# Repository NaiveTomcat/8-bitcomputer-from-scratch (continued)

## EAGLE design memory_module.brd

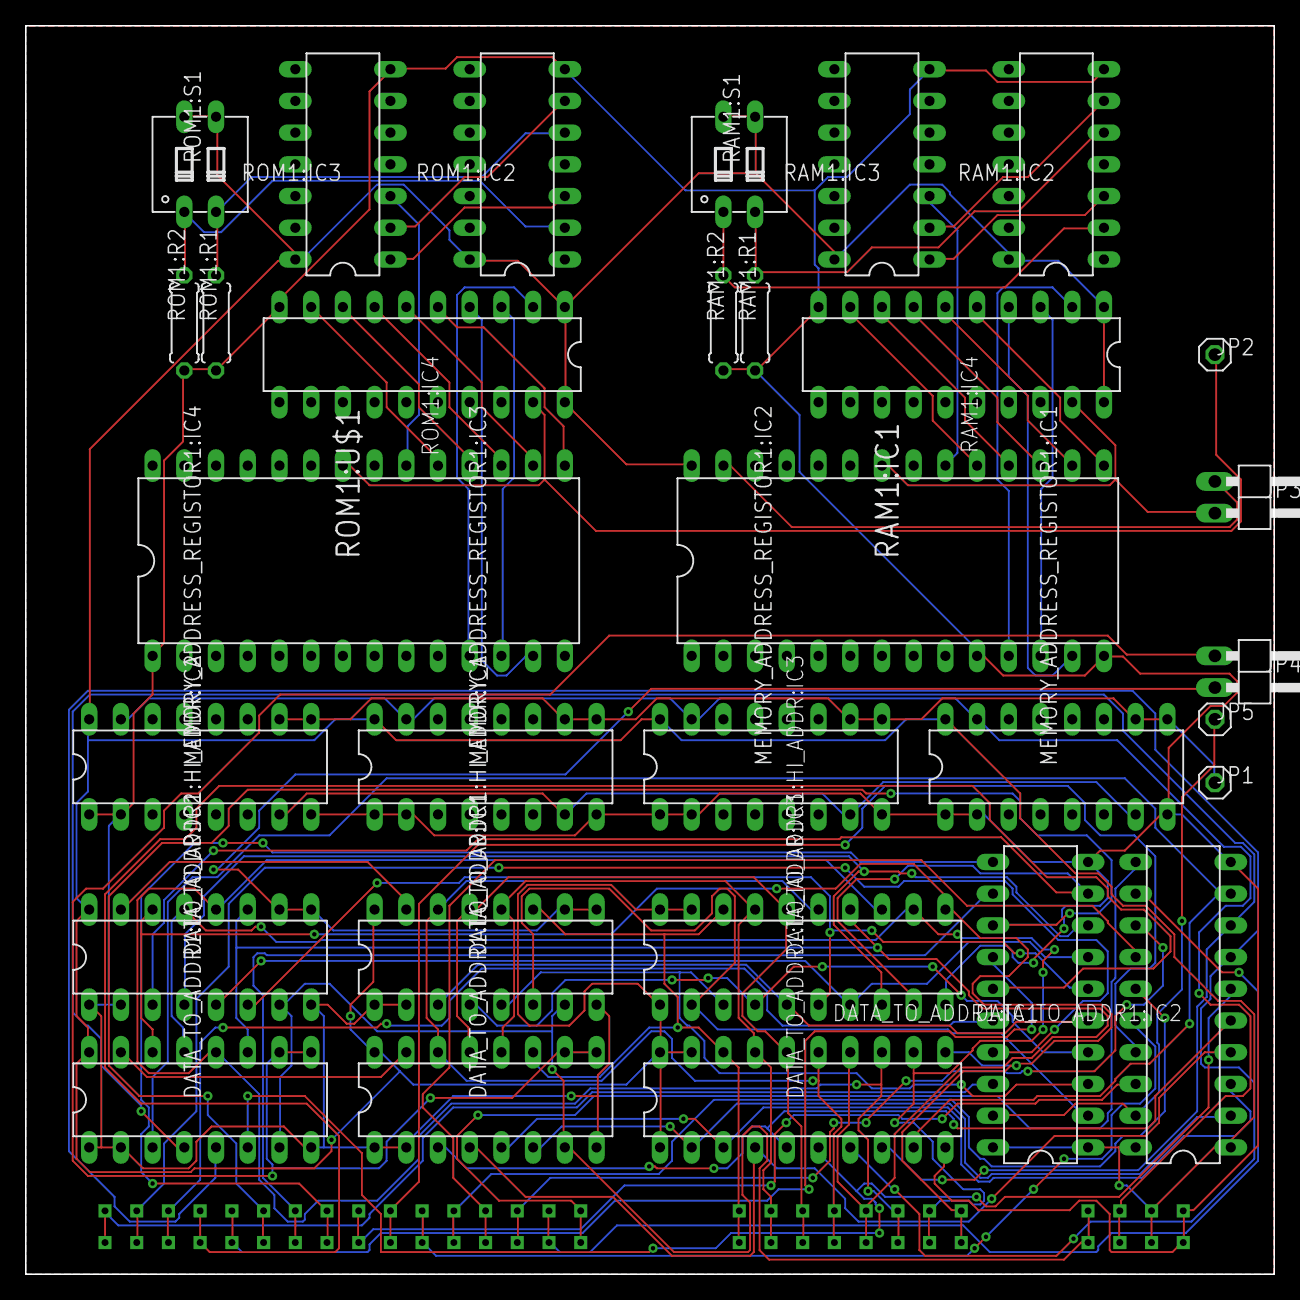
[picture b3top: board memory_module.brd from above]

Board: 2 copper layers, 100.0 x 100.0 mm, 32 parts (0 on the bottom side), 80 nets.

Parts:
DATA_TO_ADDR1:HI_ADDR:IC1, DATA_TO_ADDR1:HI_ADDR:IC2, DATA_TO_ADDR1:LO_ADDR:IC1, DATA_TO_ADDR1:LO_ADDR:IC2: 74LS173N; DIL16
DATA_TO_ADDR1:HI_ADDR:IC3, DATA_TO_ADDR1:IC1, DATA_TO_ADDR1:IC2, DATA_TO_ADDR1:LO_ADDR:IC3: 74LS245N; DIL20
JP1, JP2, JP5: 1X01
JP3, JP4: 1X02/90
MEMORY_ADDRESS_REGISTOR1:IC1, MEMORY_ADDRESS_REGISTOR1:IC2, MEMORY_ADDRESS_REGISTOR1:IC3, MEMORY_ADDRESS_REGISTOR1:IC4: 74LS173N; DIL16
RAM1:IC1: CY62256LL-PC; DIL28-6
RAM1:IC2: 74LS86N; DIL14
RAM1:IC3: 7432N; DIL14
RAM1:IC4: 74LS245N; DIL20
RAM1:R1, RAM1:R2: 0207/7
RAM1:S1: DIP02YL
ROM1:IC2: 74LS86N; DIL14
ROM1:IC3: 7432N; DIL14
ROM1:IC4: 74LS245N; DIL20
ROM1:R1, ROM1:R2: 0207/7
ROM1:S1: DIP02YL
ROM1:U$1: AT28C256-28DIP; DIL28-6
U$1: PORT_BOARD; PORT_FOOTPT

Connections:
!D2AHI: DATA_TO_ADDR1:HI_ADDR:IC1.9, DATA_TO_ADDR1:HI_ADDR:IC1.10, DATA_TO_ADDR1:HI_ADDR:IC2.9, DATA_TO_ADDR1:HI_ADDR:IC2.10, JP4.2
!D2ALI: DATA_TO_ADDR1:LO_ADDR:IC1.9, DATA_TO_ADDR1:LO_ADDR:IC1.10, DATA_TO_ADDR1:LO_ADDR:IC2.9, DATA_TO_ADDR1:LO_ADDR:IC2.10, JP4.1
!D2AO: DATA_TO_ADDR1:IC1.19, DATA_TO_ADDR1:IC2.19, JP5.1
!MARI: JP1.1, MEMORY_ADDRESS_REGISTOR1:IC1.9, MEMORY_ADDRESS_REGISTOR1:IC1.10, MEMORY_ADDRESS_REGISTOR1:IC2.9, MEMORY_ADDRESS_REGISTOR1:IC2.10, MEMORY_ADDRESS_REGISTOR1:IC3.9, MEMORY_ADDRESS_REGISTOR1:IC3.10, MEMORY_ADDRESS_REGISTOR1:IC4.9, MEMORY_ADDRESS_REGISTOR1:IC4.10
!RAMO: JP3.2, RAM1:IC1.22, RAM1:IC4.19
!RAMW: JP3.1, RAM1:IC1.27
!ROMO: JP2.1, ROM1:IC4.19, ROM1:U$1.22
A0: DATA_TO_ADDR1:IC1.18, U$1.A0, U$1.A16
A1: DATA_TO_ADDR1:IC1.17, U$1.A1, U$1.A17
A2: DATA_TO_ADDR1:IC1.16, U$1.A2, U$1.A18
A3: DATA_TO_ADDR1:IC1.15, U$1.A3, U$1.A19
A4: DATA_TO_ADDR1:IC1.14, U$1.A4, U$1.A20
A5: DATA_TO_ADDR1:IC1.13, U$1.A5, U$1.A21
A6: DATA_TO_ADDR1:IC1.12, U$1.A6, U$1.A22
A7: DATA_TO_ADDR1:IC1.11, U$1.A7, U$1.A23
A8: DATA_TO_ADDR1:IC2.18, U$1.A8, U$1.A24
A9: DATA_TO_ADDR1:IC2.17, U$1.A9, U$1.A25
A10: DATA_TO_ADDR1:IC2.16, U$1.A10, U$1.A26
A11: DATA_TO_ADDR1:IC2.15, U$1.A11, U$1.A27
A12: DATA_TO_ADDR1:IC2.14, U$1.A12, U$1.A28
A13: DATA_TO_ADDR1:IC2.13, U$1.A13, U$1.A29
A14: DATA_TO_ADDR1:IC2.12, U$1.A14, U$1.A30
A15: DATA_TO_ADDR1:IC2.11, U$1.A15, U$1.A31
CLOCK: DATA_TO_ADDR1:HI_ADDR:IC1.7, DATA_TO_ADDR1:HI_ADDR:IC2.7, DATA_TO_ADDR1:LO_ADDR:IC1.7, DATA_TO_ADDR1:LO_ADDR:IC2.7, U$1.CLK, U$1.CLK1
DATA_0: DATA_TO_ADDR1:HI_ADDR:IC1.11, DATA_TO_ADDR1:HI_ADDR:IC3.18, DATA_TO_ADDR1:LO_ADDR:IC1.11, DATA_TO_ADDR1:LO_ADDR:IC3.18, U$1.D0, U$1.D8
DATA_1: DATA_TO_ADDR1:HI_ADDR:IC1.12, DATA_TO_ADDR1:HI_ADDR:IC3.17, DATA_TO_ADDR1:LO_ADDR:IC1.12, DATA_TO_ADDR1:LO_ADDR:IC3.17, U$1.D1, U$1.D9
DATA_2: DATA_TO_ADDR1:HI_ADDR:IC1.13, DATA_TO_ADDR1:HI_ADDR:IC3.16, DATA_TO_ADDR1:LO_ADDR:IC1.13, DATA_TO_ADDR1:LO_ADDR:IC3.16, U$1.D2, U$1.D10
DATA_3: DATA_TO_ADDR1:HI_ADDR:IC1.14, DATA_TO_ADDR1:HI_ADDR:IC3.15, DATA_TO_ADDR1:LO_ADDR:IC1.14, DATA_TO_ADDR1:LO_ADDR:IC3.15, U$1.D3, U$1.D11
DATA_4: DATA_TO_ADDR1:HI_ADDR:IC2.11, DATA_TO_ADDR1:HI_ADDR:IC3.14, DATA_TO_ADDR1:LO_ADDR:IC2.11, DATA_TO_ADDR1:LO_ADDR:IC3.14, U$1.D4, U$1.D12
DATA_5: DATA_TO_ADDR1:HI_ADDR:IC2.12, DATA_TO_ADDR1:HI_ADDR:IC3.13, DATA_TO_ADDR1:LO_ADDR:IC2.12, DATA_TO_ADDR1:LO_ADDR:IC3.13, U$1.D5, U$1.D13
DATA_6: DATA_TO_ADDR1:HI_ADDR:IC2.13, DATA_TO_ADDR1:HI_ADDR:IC3.12, DATA_TO_ADDR1:LO_ADDR:IC2.13, DATA_TO_ADDR1:LO_ADDR:IC3.12, U$1.D6, U$1.D14
DATA_7: DATA_TO_ADDR1:HI_ADDR:IC2.14, DATA_TO_ADDR1:HI_ADDR:IC3.11, DATA_TO_ADDR1:LO_ADDR:IC2.14, DATA_TO_ADDR1:LO_ADDR:IC3.11, U$1.D7, U$1.D15
DATA_TO_ADDR1:HI_ADDR:CLR: DATA_TO_ADDR1:HI_ADDR:IC1.15, DATA_TO_ADDR1:HI_ADDR:IC2.15
DATA_TO_ADDR1:LO_ADDR:CLR: DATA_TO_ADDR1:LO_ADDR:IC1.15, DATA_TO_ADDR1:LO_ADDR:IC2.15
DATA_TO_ADDR1:N$16: DATA_TO_ADDR1:HI_ADDR:IC1.6, DATA_TO_ADDR1:HI_ADDR:IC3.2, DATA_TO_ADDR1:IC1.2
DATA_TO_ADDR1:N$17: DATA_TO_ADDR1:HI_ADDR:IC1.5, DATA_TO_ADDR1:HI_ADDR:IC3.3, DATA_TO_ADDR1:IC1.3
DATA_TO_ADDR1:N$18: DATA_TO_ADDR1:HI_ADDR:IC1.4, DATA_TO_ADDR1:HI_ADDR:IC3.4, DATA_TO_ADDR1:IC1.4
DATA_TO_ADDR1:N$19: DATA_TO_ADDR1:HI_ADDR:IC1.3, DATA_TO_ADDR1:HI_ADDR:IC3.5, DATA_TO_ADDR1:IC1.5
DATA_TO_ADDR1:N$20: DATA_TO_ADDR1:HI_ADDR:IC2.6, DATA_TO_ADDR1:HI_ADDR:IC3.6, DATA_TO_ADDR1:IC1.6
DATA_TO_ADDR1:N$21: DATA_TO_ADDR1:HI_ADDR:IC2.5, DATA_TO_ADDR1:HI_ADDR:IC3.7, DATA_TO_ADDR1:IC1.7
DATA_TO_ADDR1:N$22: DATA_TO_ADDR1:HI_ADDR:IC2.4, DATA_TO_ADDR1:HI_ADDR:IC3.8, DATA_TO_ADDR1:IC1.8
DATA_TO_ADDR1:N$23: DATA_TO_ADDR1:HI_ADDR:IC2.3, DATA_TO_ADDR1:HI_ADDR:IC3.9, DATA_TO_ADDR1:IC1.9
DATA_TO_ADDR1:N$24: DATA_TO_ADDR1:IC2.2, DATA_TO_ADDR1:LO_ADDR:IC1.6, DATA_TO_ADDR1:LO_ADDR:IC3.2
DATA_TO_ADDR1:N$25: DATA_TO_ADDR1:IC2.3, DATA_TO_ADDR1:LO_ADDR:IC1.5, DATA_TO_ADDR1:LO_ADDR:IC3.3
DATA_TO_ADDR1:N$26: DATA_TO_ADDR1:IC2.4, DATA_TO_ADDR1:LO_ADDR:IC1.4, DATA_TO_ADDR1:LO_ADDR:IC3.4
DATA_TO_ADDR1:N$27: DATA_TO_ADDR1:IC2.5, DATA_TO_ADDR1:LO_ADDR:IC1.3, DATA_TO_ADDR1:LO_ADDR:IC3.5
DATA_TO_ADDR1:N$28: DATA_TO_ADDR1:IC2.6, DATA_TO_ADDR1:LO_ADDR:IC2.6, DATA_TO_ADDR1:LO_ADDR:IC3.6
DATA_TO_ADDR1:N$29: DATA_TO_ADDR1:IC2.7, DATA_TO_ADDR1:LO_ADDR:IC2.5, DATA_TO_ADDR1:LO_ADDR:IC3.7
DATA_TO_ADDR1:N$30: DATA_TO_ADDR1:IC2.8, DATA_TO_ADDR1:LO_ADDR:IC2.4, DATA_TO_ADDR1:LO_ADDR:IC3.8
DATA_TO_ADDR1:N$31: DATA_TO_ADDR1:IC2.9, DATA_TO_ADDR1:LO_ADDR:IC2.3, DATA_TO_ADDR1:LO_ADDR:IC3.9
GND: DATA_TO_ADDR1:HI_ADDR:IC1.1, DATA_TO_ADDR1:HI_ADDR:IC1.2, DATA_TO_ADDR1:HI_ADDR:IC1.8, DATA_TO_ADDR1:HI_ADDR:IC2.1, DATA_TO_ADDR1:HI_ADDR:IC2.2, DATA_TO_ADDR1:HI_ADDR:IC2.8, DATA_TO_ADDR1:HI_ADDR:IC3.10, DATA_TO_ADDR1:IC1.10, DATA_TO_ADDR1:IC2.10, DATA_TO_ADDR1:LO_ADDR:IC1.1, DATA_TO_ADDR1:LO_ADDR:IC1.2, DATA_TO_ADDR1:LO_ADDR:IC1.8, DATA_TO_ADDR1:LO_ADDR:IC2.1, DATA_TO_ADDR1:LO_ADDR:IC2.2, DATA_TO_ADDR1:LO_ADDR:IC2.8, DATA_TO_ADDR1:LO_ADDR:IC3.10, MEMORY_ADDRESS_REGISTOR1:IC1.1, MEMORY_ADDRESS_REGISTOR1:IC1.2, MEMORY_ADDRESS_REGISTOR1:IC1.8, MEMORY_ADDRESS_REGISTOR1:IC2.1, MEMORY_ADDRESS_REGISTOR1:IC2.2, MEMORY_ADDRESS_REGISTOR1:IC2.8, MEMORY_ADDRESS_REGISTOR1:IC3.1, MEMORY_ADDRESS_REGISTOR1:IC3.2, MEMORY_ADDRESS_REGISTOR1:IC3.8, MEMORY_ADDRESS_REGISTOR1:IC4.1, MEMORY_ADDRESS_REGISTOR1:IC4.2, MEMORY_ADDRESS_REGISTOR1:IC4.8, RAM1:IC1.10, RAM1:IC1.14, RAM1:IC2.7, RAM1:IC3.7, RAM1:IC4.10, RAM1:R1.1, RAM1:R2.1, ROM1:IC2.7, ROM1:IC3.7, ROM1:IC4.10, ROM1:R1.1, ROM1:R2.1, ROM1:U$1.1, U$1.GND, U$1.GND1
MEMORY_ADDRESS_REGISTOR1:CLOCK: MEMORY_ADDRESS_REGISTOR1:IC1.7, MEMORY_ADDRESS_REGISTOR1:IC2.7, MEMORY_ADDRESS_REGISTOR1:IC3.7, MEMORY_ADDRESS_REGISTOR1:IC4.7
RAM1:N$1: RAM1:IC1.11, RAM1:IC4.2
RAM1:N$2: RAM1:IC1.12, RAM1:IC4.3
RAM1:N$3: RAM1:IC1.13, RAM1:IC4.4
RAM1:N$4: RAM1:IC1.15, RAM1:IC4.5
RAM1:N$5: RAM1:IC1.16, RAM1:IC4.6
RAM1:N$6: RAM1:IC1.17, RAM1:IC4.7
RAM1:N$7: RAM1:IC1.18, RAM1:IC4.8
RAM1:N$8: RAM1:IC1.19, RAM1:IC4.9
RAM1:N$23: RAM1:IC2.5, RAM1:R1.2, RAM1:S1.2
RAM1:N$24: RAM1:IC2.2, RAM1:R2.2, RAM1:S1.1
RAM1:N$27: RAM1:IC2.3, RAM1:IC3.1
RAM1:N$28: RAM1:IC2.6, RAM1:IC3.2
RAM1:N$29: RAM1:IC1.20, RAM1:IC3.3
RESET: MEMORY_ADDRESS_REGISTOR1:IC1.15, MEMORY_ADDRESS_REGISTOR1:IC2.15, MEMORY_ADDRESS_REGISTOR1:IC3.15, MEMORY_ADDRESS_REGISTOR1:IC4.15, U$1.RST, U$1.RST1
ROM1:N$1: ROM1:IC4.2, ROM1:U$1.11
ROM1:N$2: ROM1:IC4.3, ROM1:U$1.12
ROM1:N$3: ROM1:IC4.4, ROM1:U$1.13
ROM1:N$4: ROM1:IC4.5, ROM1:U$1.15
ROM1:N$5: ROM1:IC4.6, ROM1:U$1.16
ROM1:N$6: ROM1:IC4.7, ROM1:U$1.17
ROM1:N$7: ROM1:IC4.8, ROM1:U$1.18
ROM1:N$8: ROM1:IC4.9, ROM1:U$1.19
ROM1:N$23: ROM1:IC2.5, ROM1:R1.2, ROM1:S1.2
ROM1:N$24: ROM1:IC2.2, ROM1:R2.2, ROM1:S1.1
ROM1:N$27: ROM1:IC2.3, ROM1:IC3.1
ROM1:N$28: ROM1:IC2.6, ROM1:IC3.2
ROM1:N$29: ROM1:IC3.3, ROM1:U$1.20
VCC: DATA_TO_ADDR1:HI_ADDR:IC1.16, DATA_TO_ADDR1:HI_ADDR:IC2.16, DATA_TO_ADDR1:HI_ADDR:IC3.1, DATA_TO_ADDR1:HI_ADDR:IC3.19, DATA_TO_ADDR1:HI_ADDR:IC3.20, DATA_TO_ADDR1:IC1.1, DATA_TO_ADDR1:IC1.20, DATA_TO_ADDR1:IC2.1, DATA_TO_ADDR1:IC2.20, DATA_TO_ADDR1:LO_ADDR:IC1.16, DATA_TO_ADDR1:LO_ADDR:IC2.16, DATA_TO_ADDR1:LO_ADDR:IC3.1, DATA_TO_ADDR1:LO_ADDR:IC3.19, DATA_TO_ADDR1:LO_ADDR:IC3.20, MEMORY_ADDRESS_REGISTOR1:IC1.16, MEMORY_ADDRESS_REGISTOR1:IC2.16, MEMORY_ADDRESS_REGISTOR1:IC3.16, MEMORY_ADDRESS_REGISTOR1:IC4.16, RAM1:IC1.28, RAM1:IC2.14, RAM1:IC3.14, RAM1:IC4.1, RAM1:IC4.20, RAM1:S1.3, RAM1:S1.4, ROM1:IC2.14, ROM1:IC3.14, ROM1:IC4.1, ROM1:IC4.20, ROM1:S1.3, ROM1:S1.4, U$1.VCC, U$1.VCC1

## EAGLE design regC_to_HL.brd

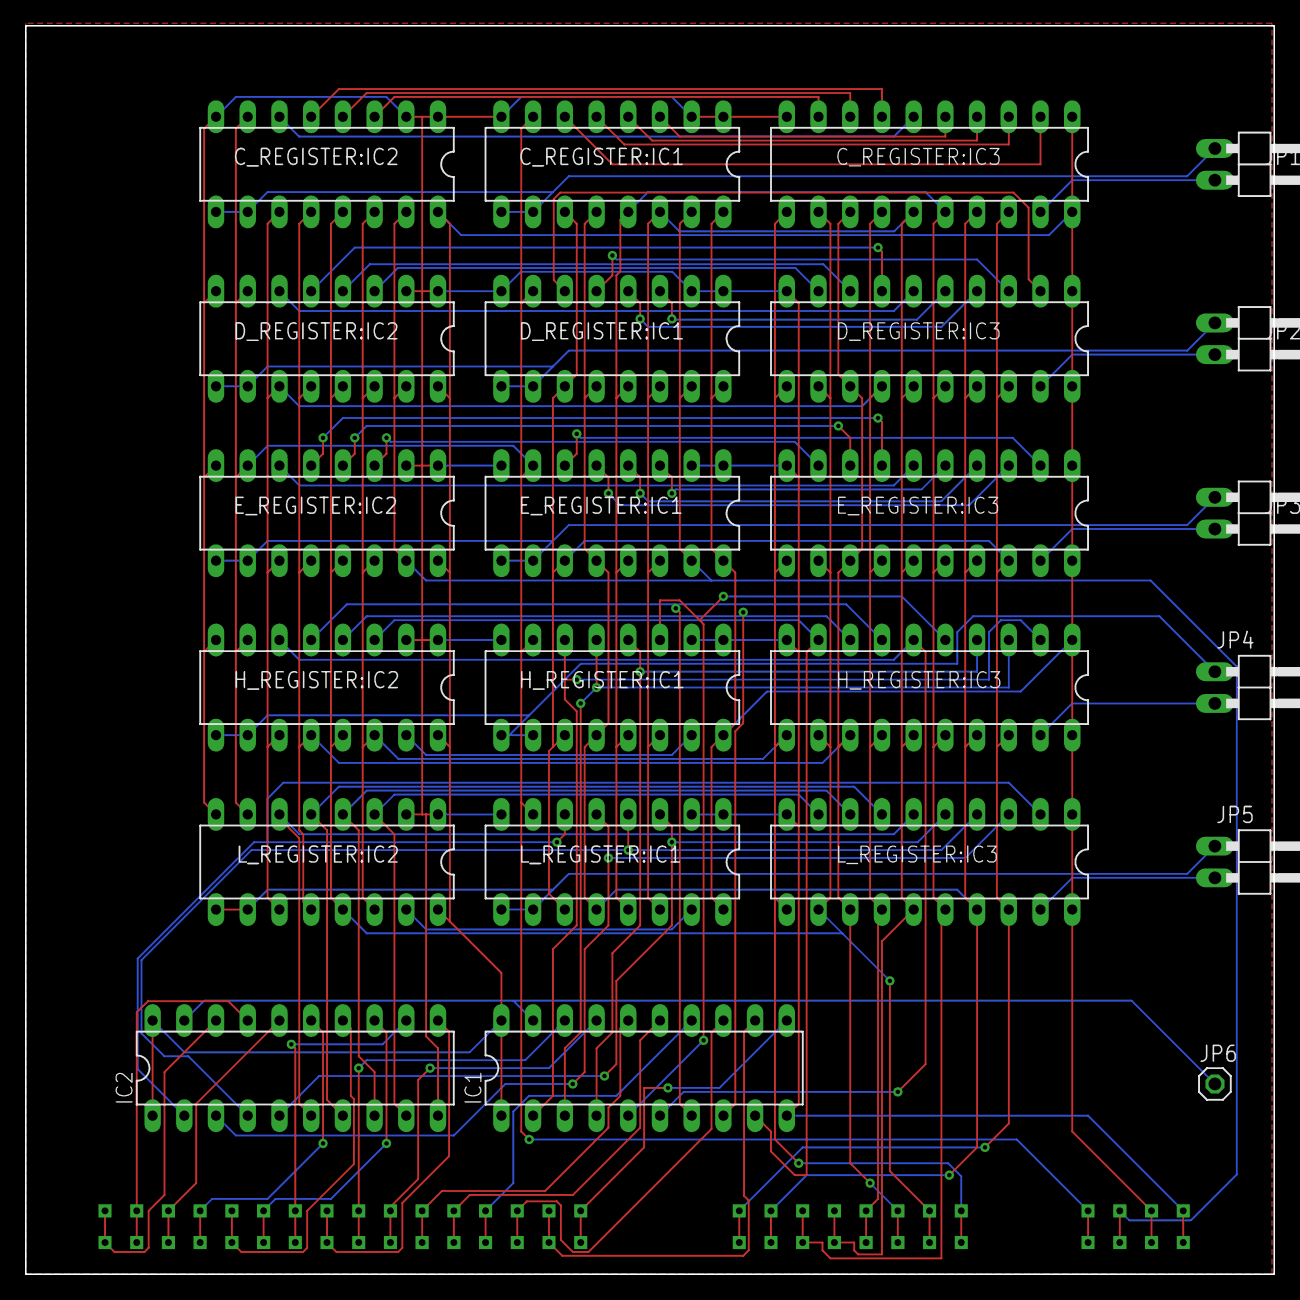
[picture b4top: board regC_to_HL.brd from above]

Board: 2 copper layers, 100.0 x 100.0 mm, 24 parts (0 on the bottom side), 81 nets.

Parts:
C_REGISTER:IC1, C_REGISTER:IC2: 74LS173N; DIL16
C_REGISTER:IC3: 74LS245N; DIL20
D_REGISTER:IC1, D_REGISTER:IC2: 74LS173N; DIL16
D_REGISTER:IC3: 74LS245N; DIL20
E_REGISTER:IC1, E_REGISTER:IC2: 74LS173N; DIL16
E_REGISTER:IC3: 74LS245N; DIL20
H_REGISTER:IC1, H_REGISTER:IC2: 74LS173N; DIL16
H_REGISTER:IC3: 74LS245N; DIL20
IC1, IC2: 74LS245N; DIL20
JP1, JP2, JP3, JP4, JP5: 1X02/90
JP6: 1X01
L_REGISTER:IC1, L_REGISTER:IC2: 74LS173N; DIL16
L_REGISTER:IC3: 74LS245N; DIL20
U$1: PORT_BOARD; PORT_FOOTPT

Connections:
!CI: C_REGISTER:IC1.9, C_REGISTER:IC1.10, C_REGISTER:IC2.9, C_REGISTER:IC2.10, JP1.1
!CO: C_REGISTER:IC3.19, JP1.2
!DI: D_REGISTER:IC1.9, D_REGISTER:IC1.10, D_REGISTER:IC2.9, D_REGISTER:IC2.10, JP2.1
!DO: D_REGISTER:IC3.19, JP2.2
!EI: E_REGISTER:IC1.9, E_REGISTER:IC1.10, E_REGISTER:IC2.9, E_REGISTER:IC2.10, JP3.1
!EO: E_REGISTER:IC3.19, JP3.2
!HI: H_REGISTER:IC1.9, H_REGISTER:IC1.10, H_REGISTER:IC2.9, H_REGISTER:IC2.10, JP4.1
!HL_TO_ADDR: IC1.19, IC2.19, JP6.1
!HO: H_REGISTER:IC3.19, JP4.2
!LI: JP5.1, L_REGISTER:IC1.9, L_REGISTER:IC1.10, L_REGISTER:IC2.9, L_REGISTER:IC2.10
!LO: JP5.2, L_REGISTER:IC3.19
A0: IC2.18, U$1.A0, U$1.A16
A1: IC2.17, U$1.A1, U$1.A17
A2: IC2.16, U$1.A2, U$1.A18
A3: IC2.15, U$1.A3, U$1.A19
A4: IC2.14, U$1.A4, U$1.A20
A5: IC2.13, U$1.A5, U$1.A21
A6: IC2.12, U$1.A6, U$1.A22
A7: IC2.11, U$1.A7, U$1.A23
A8: IC1.18, U$1.A8, U$1.A24
A9: IC1.17, U$1.A9, U$1.A25
A10: IC1.16, U$1.A10, U$1.A26
A11: IC1.15, U$1.A11, U$1.A27
A12: IC1.14, U$1.A12, U$1.A28
A13: IC1.13, U$1.A13, U$1.A29
A14: IC1.12, U$1.A14, U$1.A30
A15: IC1.11, U$1.A15, U$1.A31
CLOCK1: C_REGISTER:IC1.7, C_REGISTER:IC2.7, D_REGISTER:IC1.7, D_REGISTER:IC2.7, E_REGISTER:IC1.7, E_REGISTER:IC2.7, H_REGISTER:IC1.7, H_REGISTER:IC2.7, L_REGISTER:IC1.7, L_REGISTER:IC2.7, U$1.CLK, U$1.CLK1
C_REGISTER:UB_0: C_REGISTER:IC1.6, C_REGISTER:IC3.2
C_REGISTER:UB_1: C_REGISTER:IC1.5, C_REGISTER:IC3.3
C_REGISTER:UB_2: C_REGISTER:IC1.4, C_REGISTER:IC3.4
C_REGISTER:UB_3: C_REGISTER:IC1.3, C_REGISTER:IC3.5
C_REGISTER:UB_4: C_REGISTER:IC2.6, C_REGISTER:IC3.6
C_REGISTER:UB_5: C_REGISTER:IC2.5, C_REGISTER:IC3.7
C_REGISTER:UB_6: C_REGISTER:IC2.4, C_REGISTER:IC3.8
C_REGISTER:UB_7: C_REGISTER:IC2.3, C_REGISTER:IC3.9
DATA_0: C_REGISTER:IC1.11, C_REGISTER:IC3.18, D_REGISTER:IC1.11, D_REGISTER:IC3.18, E_REGISTER:IC1.11, E_REGISTER:IC3.18, H_REGISTER:IC1.11, H_REGISTER:IC3.18, L_REGISTER:IC1.11, L_REGISTER:IC3.18, U$1.D0, U$1.D8
DATA_1: C_REGISTER:IC1.12, C_REGISTER:IC3.17, D_REGISTER:IC1.12, D_REGISTER:IC3.17, E_REGISTER:IC1.12, E_REGISTER:IC3.17, H_REGISTER:IC1.12, H_REGISTER:IC3.17, L_REGISTER:IC1.12, L_REGISTER:IC3.17, U$1.D1, U$1.D9
DATA_2: C_REGISTER:IC1.13, C_REGISTER:IC3.16, D_REGISTER:IC1.13, D_REGISTER:IC3.16, E_REGISTER:IC1.13, E_REGISTER:IC3.16, H_REGISTER:IC1.13, H_REGISTER:IC3.16, L_REGISTER:IC1.13, L_REGISTER:IC3.16, U$1.D2, U$1.D10
DATA_3: C_REGISTER:IC1.14, C_REGISTER:IC3.15, D_REGISTER:IC1.14, D_REGISTER:IC3.15, E_REGISTER:IC1.14, E_REGISTER:IC3.15, H_REGISTER:IC1.14, H_REGISTER:IC3.15, L_REGISTER:IC1.14, L_REGISTER:IC3.15, U$1.D3, U$1.D11
DATA_4: C_REGISTER:IC2.11, C_REGISTER:IC3.14, D_REGISTER:IC2.11, D_REGISTER:IC3.14, E_REGISTER:IC2.11, E_REGISTER:IC3.14, H_REGISTER:IC2.11, H_REGISTER:IC3.14, L_REGISTER:IC2.11, L_REGISTER:IC3.14, U$1.D4, U$1.D12
DATA_5: C_REGISTER:IC2.12, C_REGISTER:IC3.13, D_REGISTER:IC2.12, D_REGISTER:IC3.13, E_REGISTER:IC2.12, E_REGISTER:IC3.13, H_REGISTER:IC2.12, H_REGISTER:IC3.13, L_REGISTER:IC2.12, L_REGISTER:IC3.13, U$1.D5, U$1.D13
DATA_6: C_REGISTER:IC2.13, C_REGISTER:IC3.12, D_REGISTER:IC2.13, D_REGISTER:IC3.12, E_REGISTER:IC2.13, E_REGISTER:IC3.12, H_REGISTER:IC2.13, H_REGISTER:IC3.12, L_REGISTER:IC2.13, L_REGISTER:IC3.12, U$1.D6, U$1.D14
DATA_7: C_REGISTER:IC2.14, C_REGISTER:IC3.11, D_REGISTER:IC2.14, D_REGISTER:IC3.11, E_REGISTER:IC2.14, E_REGISTER:IC3.11, H_REGISTER:IC2.14, H_REGISTER:IC3.11, L_REGISTER:IC2.14, L_REGISTER:IC3.11, U$1.D7, U$1.D15
D_REGISTER:UB_0: D_REGISTER:IC1.6, D_REGISTER:IC3.2
D_REGISTER:UB_1: D_REGISTER:IC1.5, D_REGISTER:IC3.3
D_REGISTER:UB_2: D_REGISTER:IC1.4, D_REGISTER:IC3.4
D_REGISTER:UB_3: D_REGISTER:IC1.3, D_REGISTER:IC3.5
D_REGISTER:UB_4: D_REGISTER:IC2.6, D_REGISTER:IC3.6
D_REGISTER:UB_5: D_REGISTER:IC2.5, D_REGISTER:IC3.7
D_REGISTER:UB_6: D_REGISTER:IC2.4, D_REGISTER:IC3.8
D_REGISTER:UB_7: D_REGISTER:IC2.3, D_REGISTER:IC3.9
E_REGISTER:UB_0: E_REGISTER:IC1.6, E_REGISTER:IC3.2
E_REGISTER:UB_1: E_REGISTER:IC1.5, E_REGISTER:IC3.3
E_REGISTER:UB_2: E_REGISTER:IC1.4, E_REGISTER:IC3.4
E_REGISTER:UB_3: E_REGISTER:IC1.3, E_REGISTER:IC3.5
E_REGISTER:UB_4: E_REGISTER:IC2.6, E_REGISTER:IC3.6
E_REGISTER:UB_5: E_REGISTER:IC2.5, E_REGISTER:IC3.7
E_REGISTER:UB_6: E_REGISTER:IC2.4, E_REGISTER:IC3.8
E_REGISTER:UB_7: E_REGISTER:IC2.3, E_REGISTER:IC3.9
GND: C_REGISTER:IC1.1, C_REGISTER:IC1.2, C_REGISTER:IC1.8, C_REGISTER:IC2.1, C_REGISTER:IC2.2, C_REGISTER:IC2.8, C_REGISTER:IC3.10, D_REGISTER:IC1.1, D_REGISTER:IC1.2, D_REGISTER:IC1.8, D_REGISTER:IC2.1, D_REGISTER:IC2.2, D_REGISTER:IC2.8, D_REGISTER:IC3.10, E_REGISTER:IC1.1, E_REGISTER:IC1.2, E_REGISTER:IC1.8, E_REGISTER:IC2.1, E_REGISTER:IC2.2, E_REGISTER:IC2.8, E_REGISTER:IC3.10, H_REGISTER:IC1.1, H_REGISTER:IC1.2, H_REGISTER:IC1.8, H_REGISTER:IC2.1, H_REGISTER:IC2.2, H_REGISTER:IC2.8, H_REGISTER:IC3.10, IC1.10, IC2.10, L_REGISTER:IC1.1, L_REGISTER:IC1.2, L_REGISTER:IC1.8, L_REGISTER:IC2.1, L_REGISTER:IC2.2, L_REGISTER:IC2.8, L_REGISTER:IC3.10, U$1.GND, U$1.GND1
H_REGISTER:CLR: H_REGISTER:IC1.15, H_REGISTER:IC2.15
L_REGISTER:CLR: L_REGISTER:IC1.15, L_REGISTER:IC2.15
unnamed: C_REGISTER:IC1.15, C_REGISTER:IC2.15, D_REGISTER:IC1.15, D_REGISTER:IC2.15, E_REGISTER:IC1.15, E_REGISTER:IC2.15, U$1.RST, U$1.RST1
unnamed: H_REGISTER:IC1.6, H_REGISTER:IC3.2, IC1.2
unnamed: H_REGISTER:IC1.5, H_REGISTER:IC3.3, IC1.3
unnamed: H_REGISTER:IC1.4, H_REGISTER:IC3.4, IC1.4
unnamed: H_REGISTER:IC1.3, H_REGISTER:IC3.5, IC1.5
unnamed: H_REGISTER:IC2.6, H_REGISTER:IC3.6, IC1.6
unnamed: H_REGISTER:IC2.5, H_REGISTER:IC3.7, IC1.7
unnamed: H_REGISTER:IC2.4, H_REGISTER:IC3.8, IC1.8
unnamed: H_REGISTER:IC2.3, H_REGISTER:IC3.9, IC1.9
unnamed: IC2.2, L_REGISTER:IC1.6, L_REGISTER:IC3.2
unnamed: IC2.3, L_REGISTER:IC1.5, L_REGISTER:IC3.3
unnamed: IC2.4, L_REGISTER:IC1.4, L_REGISTER:IC3.4
unnamed: IC2.5, L_REGISTER:IC1.3, L_REGISTER:IC3.5
unnamed: IC2.6, L_REGISTER:IC2.6, L_REGISTER:IC3.6
unnamed: IC2.7, L_REGISTER:IC2.5, L_REGISTER:IC3.7
unnamed: IC2.8, L_REGISTER:IC2.4, L_REGISTER:IC3.8
unnamed: IC2.9, L_REGISTER:IC2.3, L_REGISTER:IC3.9
VCC: C_REGISTER:IC1.16, C_REGISTER:IC2.16, C_REGISTER:IC3.1, C_REGISTER:IC3.20, D_REGISTER:IC1.16, D_REGISTER:IC2.16, D_REGISTER:IC3.1, D_REGISTER:IC3.20, E_REGISTER:IC1.16, E_REGISTER:IC2.16, E_REGISTER:IC3.1, E_REGISTER:IC3.20, H_REGISTER:IC1.16, H_REGISTER:IC2.16, H_REGISTER:IC3.1, H_REGISTER:IC3.20, IC1.1, IC1.20, IC2.1, IC2.20, L_REGISTER:IC1.16, L_REGISTER:IC2.16, L_REGISTER:IC3.1, L_REGISTER:IC3.20, U$1.VCC, U$1.VCC1

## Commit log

2020-05-07 Initialize repo
2020-05-07 Added ALU with ADD SUB AND OR and XOR
2020-05-09 completed DATA_TO_ADDR, ALU and Program Counter/Instruction Pointer
2020-05-09 RAM Module halfway done, waiting to add method to manually program the RAM
2020-05-10 Added EEPROM Module and completed SRAM Module, all wired up
2020-05-11 Added something about outter bus
2020-05-12 Added Regigter A, Register D and ALU module and its PCB
2020-05-12 added garber result and BOM for Register A, B and ALU module
2020-05-12 Added Register C to HL and HL_TO_ADDR module and gerber and BOM
2020-05-12 Added Memory Module and its pcb with gerber file and BOM
2020-05-13 Finished all moduled except Logic Control Unit and modified ALU logic
2020-05-14 Finished all design
2020-05-14 Added final BOM
